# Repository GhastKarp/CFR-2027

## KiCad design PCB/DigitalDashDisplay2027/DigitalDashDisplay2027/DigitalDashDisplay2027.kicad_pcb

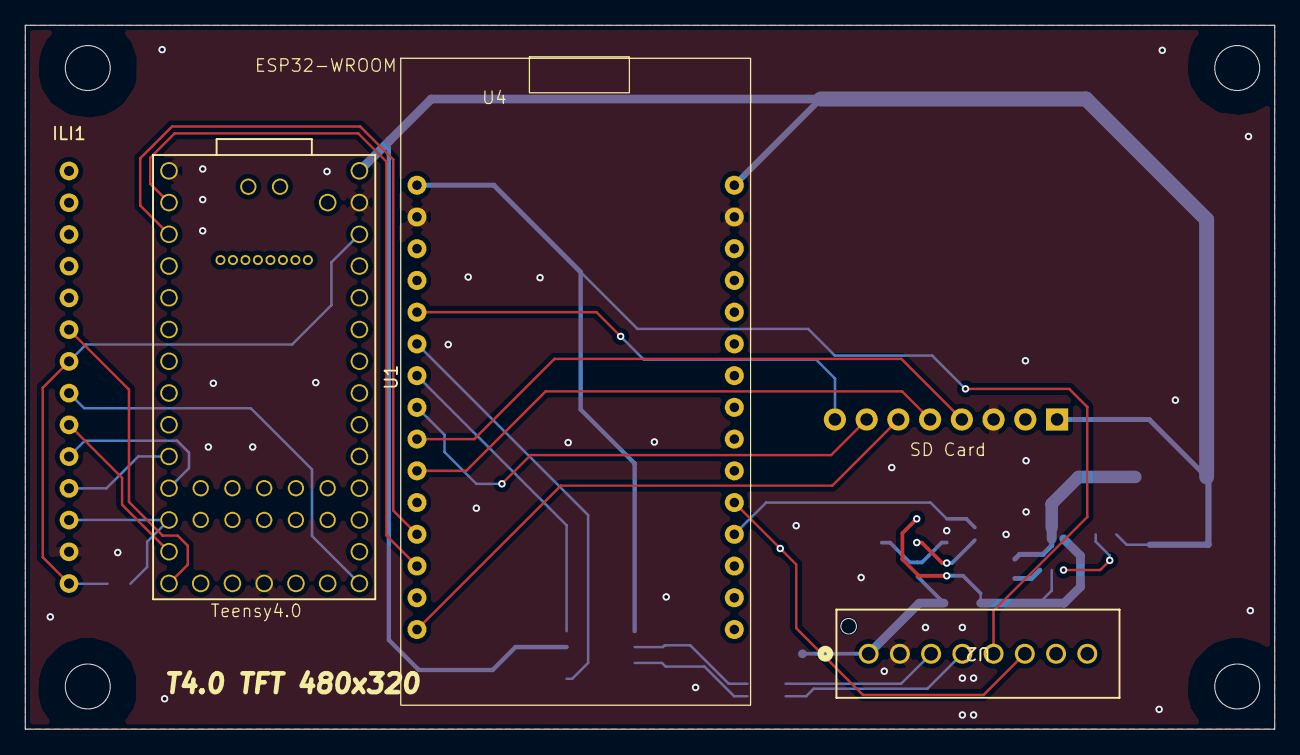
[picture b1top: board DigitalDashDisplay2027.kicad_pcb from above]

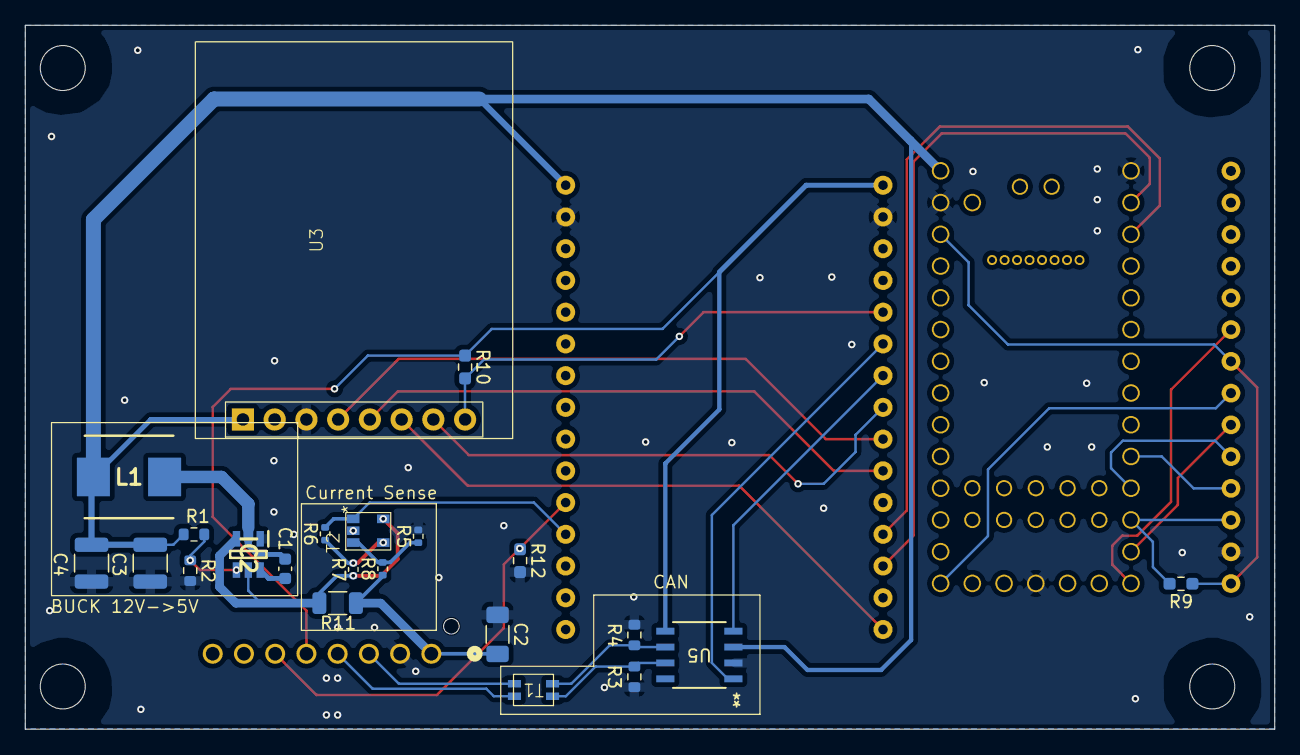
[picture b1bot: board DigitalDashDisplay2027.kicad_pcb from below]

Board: 2 copper layers, 100.0 x 56.3 mm, 26 parts (22 on the bottom side), 32 nets.

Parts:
C1: CC0603KRX7R7BB104; C_0603_1608Metric
C2: C3216X5R1E476MTJ00E; C_1206_3216Metric_Pad1.33x1.80mm_HandSolder
C3, C4: CL32A226KOJNNNE; C_1210_3225Metric
IC2: LMR51430YDDCR; SOT95P280X110-6N
ILI1: ILI9488
L1: PA4341.682ANLT; INDPM7166X300N
R1: ERA-3AED104V; R_0603_1608Metric
R2: ERJ-3EKF1372V; R_0603_1608Metric
R3, R4: 60; R_0603_1608Metric
R5, R6: 1.07M; R_0402_1005Metric
R7, R8: 2k; R_0402_1005Metric
R9, R10, R12: 10k; R_0603_1608Metric_Pad0.98x0.95mm_HandSolder
R11: CSR1206FT50L0; R_1206_3216Metric
T1: AC1210-110-C
T2: NCS2005SN1T1G
U1: Teensy4.0; Teensy40_SMT
U2: CONN08_533750810_MOL
U3: Adafruit 254
U4: ESP32
U5: TCAN1051VDRQ1; D8_TEX

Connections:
+5V: C3.1, C4.1, L1.2, R1.1, U1.33 (VIN), U3.1 (5V), U4.1 (VIN), U5.3 (VCC)
/3V3_ESP: R10.1, U2.5 (1), U4.30 (3V3), U5.5 (VIO)
/3V3_Teen: ILI1.7 (LED), ILI1.14 (VCC), R9.1, U1.31 (3V3)
/+12V: IC2.3 (VIN), IC2.5 (EN), R7.1, R11.1, T2.5 (V+)
/CAN Hi: T1.4 (AB), U2.4
/CAN Lo: T1.3 (SA), U2.3
/CANRx: U4.25 (RX2), U5.1 (TXD)
/CANTx: U4.24 (TX2), U5.4 (RXD)
/CurrentSense: C2.2, R8.1, R11.2, U2.1
/Current_0-3V3: R6.2, T2.1, U4.12 (D34)
/DAQ_Button: R12.1, U2.6 (2), U4.11 (D35)
/DC: ILI1.10 (DC/RS), U1.11 (9_OUT1C)
/GND: C2.1, C3.2, C4.2, IC2.1 (GND), ILI1.13 (Ground), R2.2, R3.2, R4.1, R5.2, R12.2, T2.2 (V-), U1.1 (GND), U1.17 (GND), U1.32 (GND), U2.2, U3.3 (GND), U4.2 (GND), U4.29 (GND), U5.2 (GND)
/Reset: ILI1.11 (Reset), U1.10 (8_TX2_IN1)
/SD_CD: R10.2, U3.8 (CD), U4.26 (D4)
/SD_CLK: U3.4 (CLK), U4.22 (D10)
/SD_CS: U3.7 (CS), U4.23 (D5)
/SD_MISO: U3.5 (D0), U4.21 (D19)
/SD_MOSI: U3.6 (DI), U4.16 (D23)
/TFT_CS: ILI1.12 (CS), R9.2, U1.12 (10_CS_MQSR)
/TFT_Clk: ILI1.8 (SCK), U1.20 (13_SCK_CRX1_LED)
/TFT_MISO: ILI1.6 (MISO), U1.14 (12_MISO_MQSL)
/TFT_MOSI: ILI1.9 (MOSI), U1.13 (11_MOSI_CTX1)
/TIn_EOut: U1.2 (0_RX1_CRX2_CS1), U4.18 (TX0)
/TOut_EIn: U1.3 (1_TX1_CTX2_MISO1), U4.19 (RX0)
unnamed: C1.1, IC2.6 (CB)
unnamed: IC2.4 (FB), R1.2, R2.1
unnamed: C1.2, IC2.2 (SW), L1.1
unnamed: R3.1, T1.1 (AA), U5.7 (CANH)
unnamed: R4.2, T1.2 (SB), U5.6 (CANL)
unnamed: R5.1, R8.2, T2.3 (+)
unnamed: R6.1, R7.2, T2.4 (-)

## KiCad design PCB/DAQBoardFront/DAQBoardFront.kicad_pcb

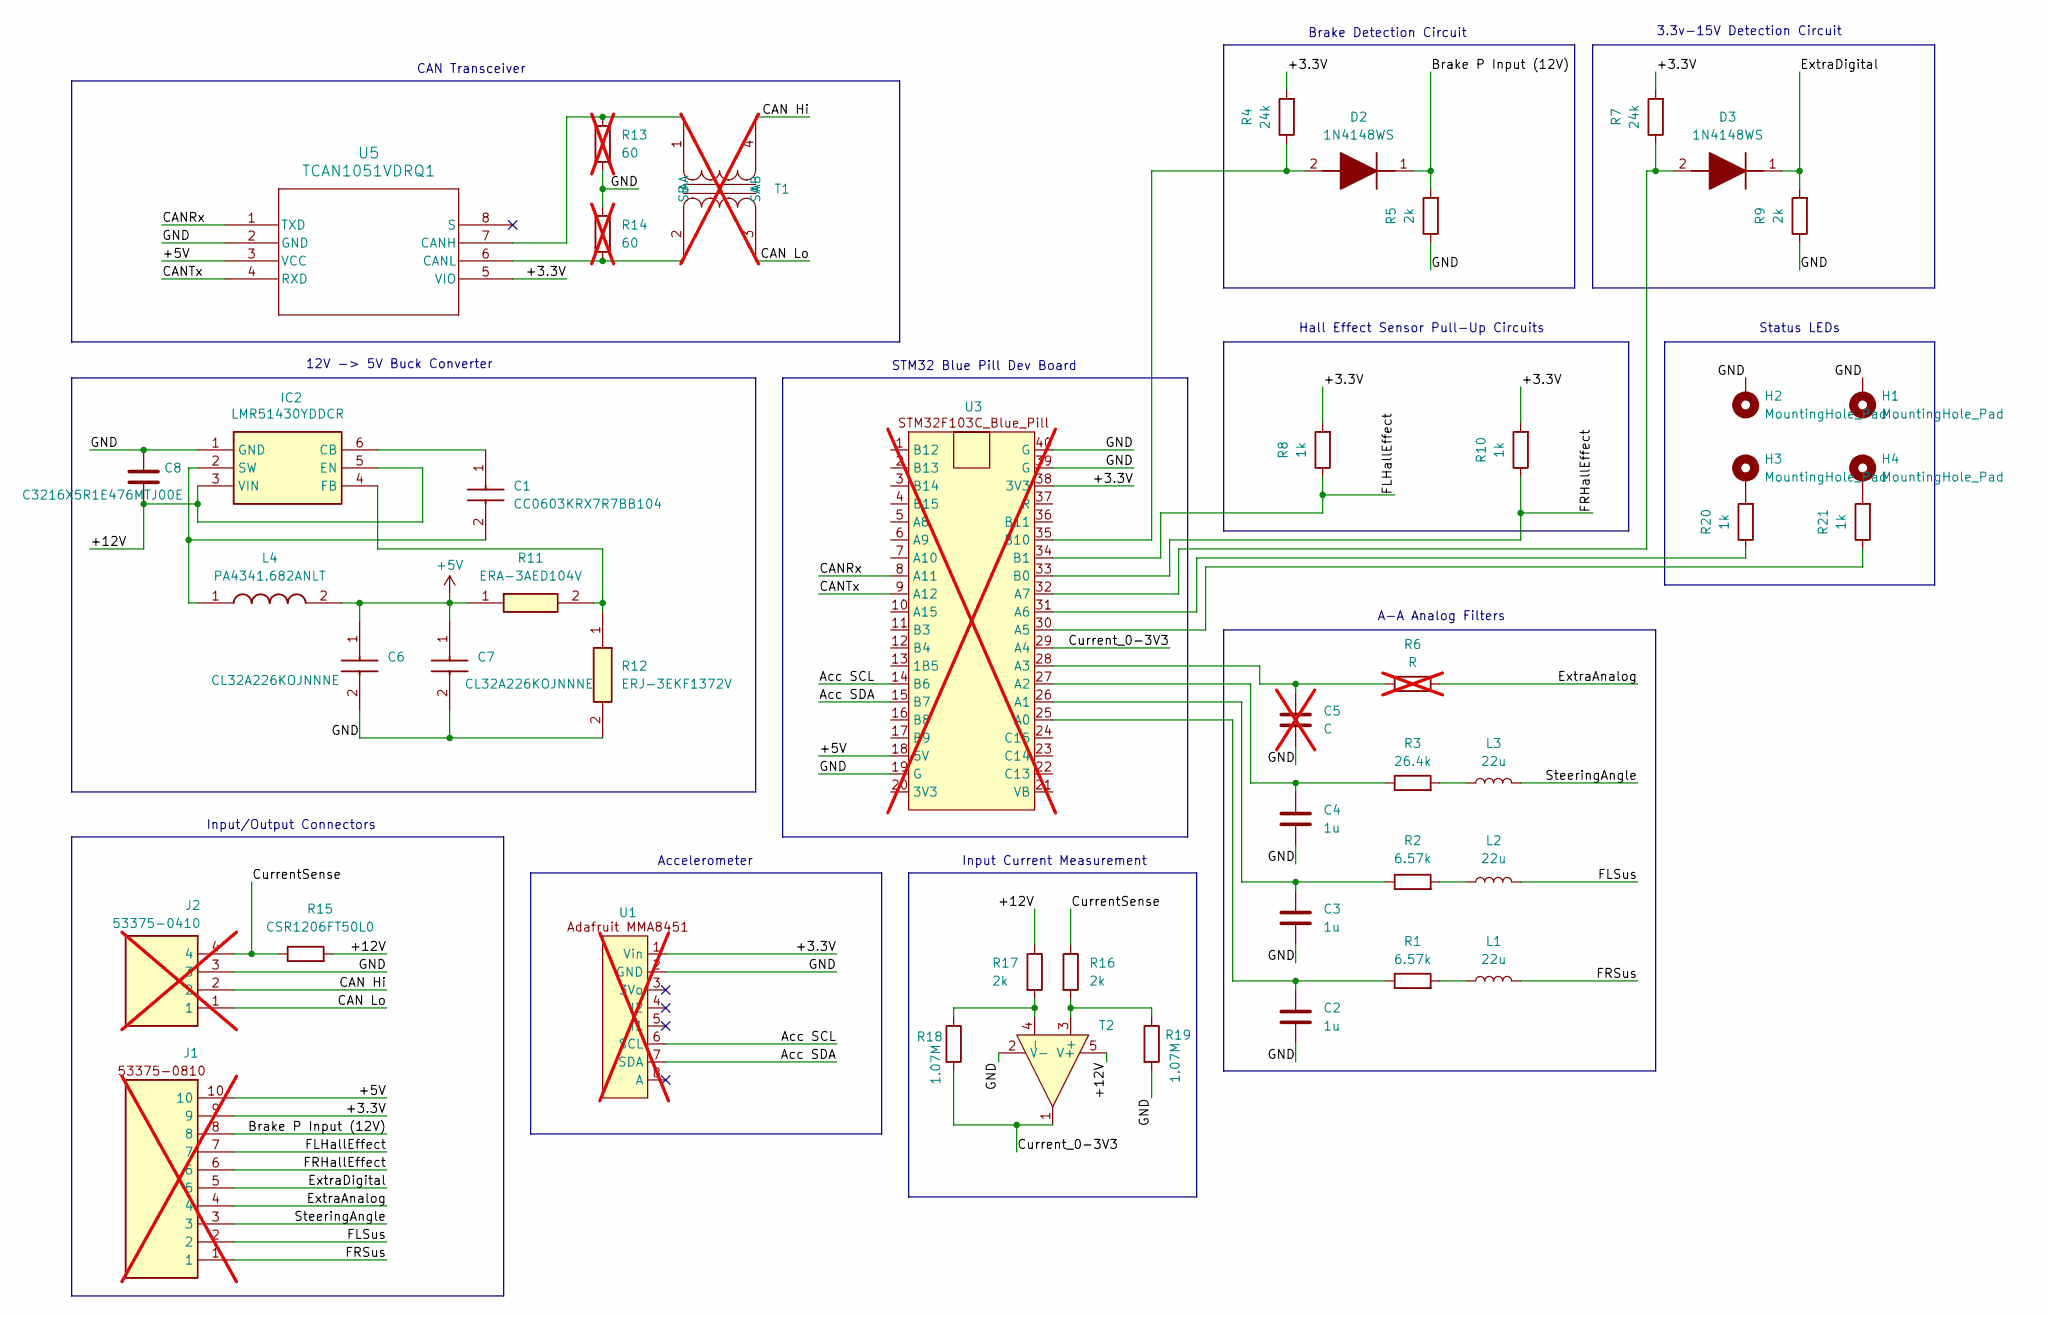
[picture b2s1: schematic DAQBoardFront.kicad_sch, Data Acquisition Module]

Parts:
C1: CC0603KRX7R7BB104; C_0603_1608Metric; Manufacturer_Part_Number CL05B104KO5NNNC; Mouser Part Number 187-CL05B104KO5NNNC
C2, C3, C4: 1u; C_0603_1608Metric_Pad1.08x0.95mm_HandSolder
C5: C; C_0603_1608Metric_Pad1.08x0.95mm_HandSolder; not fitted
C6, C7: CL32A226KOJNNNE; C_1210_3225Metric; Manufacturer_Part_Number CL32A226KOJNNNE
C8: C3216X5R1E476MTJ00E; C_1206_3216Metric_Pad1.33x1.80mm_HandSolder
D2, D3: 1N4148WS; SODFL2512X90N; Mouser Part Number 512-1N4148WS
H1, H2, H3, H4: MountingHole_Pad; PinHeader_1x01_P1.00mm_Vertical
IC2: LMR51430YDDCR; SOT95P280X110-6N; Manufacturer_Part_Number LMR51430YDDCR; Mouser Part Number 595-LMR51430YDDCR
J1: CONN10_533751010_MOL; not fitted
J2: 53375-0410; 0533750410; Mouser Part Number 538-53375-0410; not fitted
L1, L2, L3: 22u; L_0805_2012Metric_Pad1.05x1.20mm_HandSolder
L4: PA4341.682ANLT; INDPM7166X300N; Manufacturer_Part_Number PA4341.682ANLT; Mouser Part Number 673-PA4341.682ANLT
R1, R2: 6.57k; R_0603_1608Metric_Pad0.98x0.95mm_HandSolder
R3: 26.4k; R_0603_1608Metric_Pad0.98x0.95mm_HandSolder
R4, R7: 24k; LED_0603_1608Metric_Pad1.05x0.95mm_HandSolder; Rating 1/4W
R5, R9: 2k; R_0603_1608Metric_Pad0.98x0.95mm_HandSolder; Rating 1/4W
R6: R; R_0603_1608Metric_Pad0.98x0.95mm_HandSolder; not fitted
R8, R10, R20, R21: 1k; R_0603_1608Metric_Pad0.98x0.95mm_HandSolder; Rating 1/4W
R11: ERA-3AED104V; R_0603_1608Metric; Manufacturer_Part_Number ERA-3AED104V; Mouser Part Number 667-ERA-3AED104V
R12: ERJ-3EKF1372V; R_0603_1608Metric; Mouser Part Number 667-ERJ-3EKF1372V
R13, R14: 60; R_0603_1608Metric; not fitted
R15: CSR1206FT50L0; R_1206_3216Metric
R16, R17: 2k; R_0402_1005Metric
R18, R19: 1.07M; R_0402_1005Metric
T1: AC1210-110-C; not fitted
T2: NCS2005SN1T1G
U1: MODULE_2019; not fitted
U3: Blue-Pill; not fitted
U5: TCAN1051VDRQ1; D8_TEX

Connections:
+5V: C6.1, C7.1, J1.10, L4.2, R11.1, U3.18 (5V), U5.3 (VCC)
/+3.3V: J1.9, R4.2, R7.2, R8.2, R10.2, U1.1 (Vin), U3.38 (3V3), U5.5 (VIO)
/+12V: C8.2, IC2.3 (VIN), IC2.5 (EN), R15.2, R17.1, T2.5 (V+)
/Acc SCL: U1.6 (SCL), U3.14 (B6)
/Acc SDA: U1.7 (SDA), U3.15 (B7)
/Brake P Input (12V): D2.1 (K), J1.8, R5.2
/CAN Hi: J2.2, T1.4 (AB)
/CAN Lo: J2.1, T1.3 (SA)
/CANRx: U3.8 (A11), U5.1 (TXD)
/CANTx: U3.9 (A12), U5.4 (RXD)
/CurrentSense: J2.4, R15.1, R16.1
/Current_0-3V3: R18.2, T2.1, U3.29 (A4)
/ExtraAnalog: J1.4, R6.2
/ExtraDigital: D3.1 (K), J1.5, R9.2
/FLHallEffect: J1.7, R8.1, U3.34 (B1)
/FLSus: J1.2, L2.2
/FRHallEffect: J1.6, R10.1, U3.33 (B0)
/FRSus: J1.1, L1.2
/GND: C2.2, C3.2, C4.2, C5.2, C6.2, C7.2, C8.1, H1.1 (1_1), H2.1 (1_1), IC2.1 (GND), J2.3, R5.1, R9.1, R12.2, R13.2, R14.1, R19.2, T2.2 (V-), U1.2 (GND), U3.19 (G), U3.39 (G), U3.40 (G), U5.2 (GND)
/SteeringAngle: J1.3, L3.2
unnamed: D2.2 (A), R4.1, U3.35 (B10)
unnamed: D3.2 (A), R7.1, U3.32 (A7)
unnamed: H3.1 (1_1), R20.2
unnamed: H4.1 (1_1), R21.2
unnamed: C1.1, IC2.6 (CB)
unnamed: IC2.4 (FB), R11.2, R12.1
unnamed: C1.2, IC2.2 (SW), L4.1
unnamed: L1.1, R1.2
unnamed: L2.1, R2.2
unnamed: L3.1, R3.2
unnamed: R13.1, T1.1 (AA), U5.7 (CANH)
unnamed: R14.2, T1.2 (SB), U5.6 (CANL)
unnamed: R16.2, R19.1, T2.3 (+)
unnamed: R17.2, R18.1, T2.4 (-)
unnamed: C2.1, R1.1, U3.25 (A0)
unnamed: C3.1, R2.1, U3.26 (A1)
unnamed: C4.1, R3.1, U3.27 (A2)
unnamed: C5.1, R6.1, U3.28 (A3)
unnamed: R21.1, U3.30 (A5)
unnamed: R20.1, U3.31 (A6)

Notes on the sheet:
A-A Analog Filters
Hall Effect Sensor Pull-Up Circuits
Status LEDs
Brake Detection Circuit
Input/Output Connectors
12V -> 5V Buck Converter
Accelerometer
Input Current Measurement
3.3v-15V Detection Circuit
CAN Transceiver
STM32 Blue Pill Dev Board

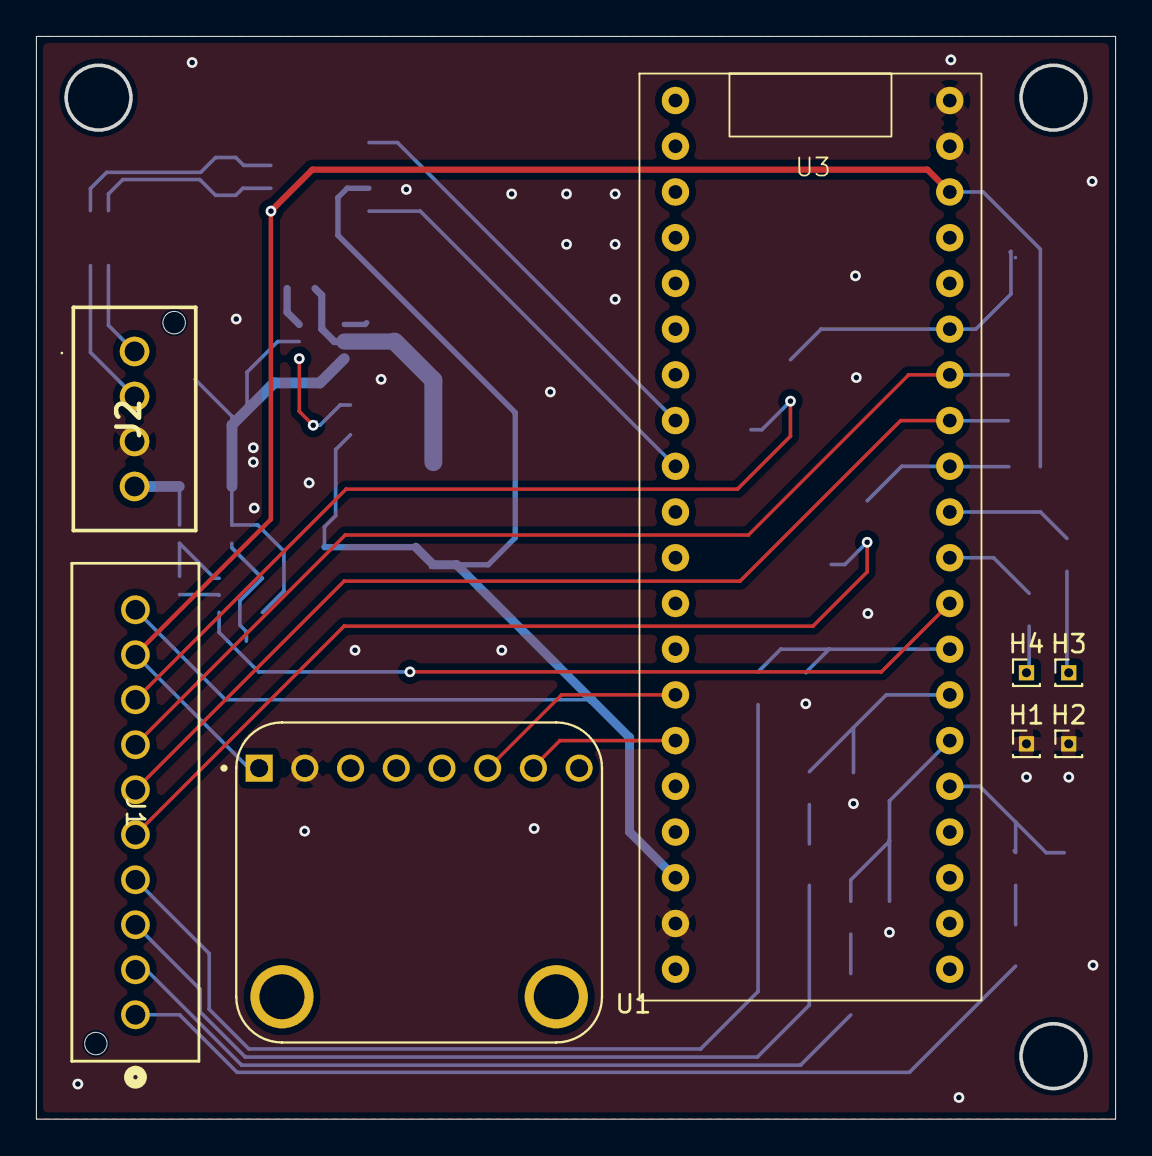
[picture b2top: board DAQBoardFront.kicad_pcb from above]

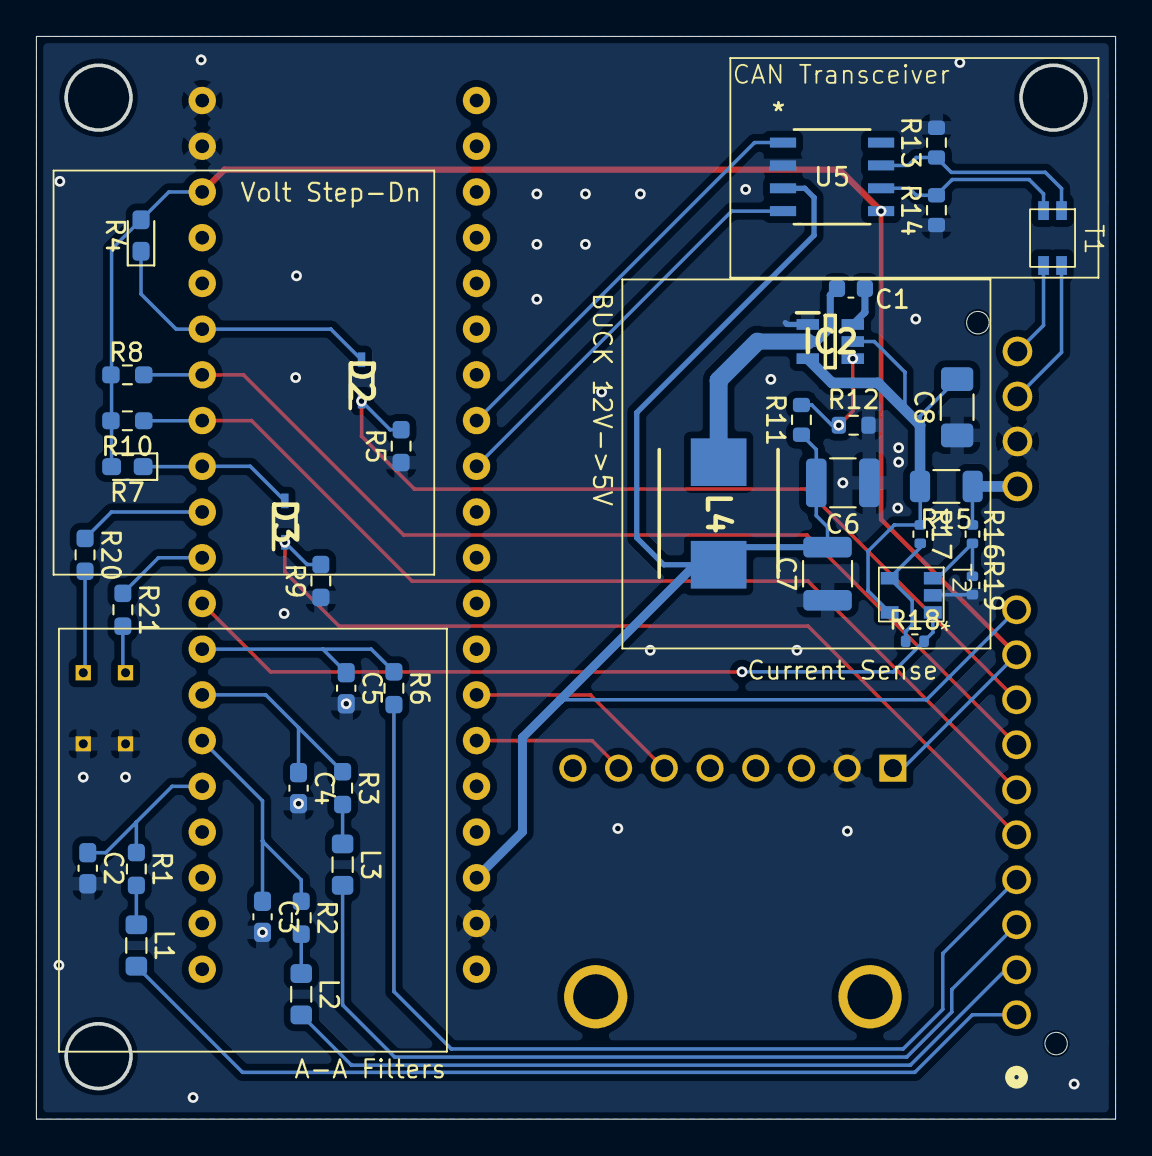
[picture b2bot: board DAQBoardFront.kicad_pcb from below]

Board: 2 copper layers, 59.8 x 60.0 mm, 47 parts (39 on the bottom side), 40 nets.

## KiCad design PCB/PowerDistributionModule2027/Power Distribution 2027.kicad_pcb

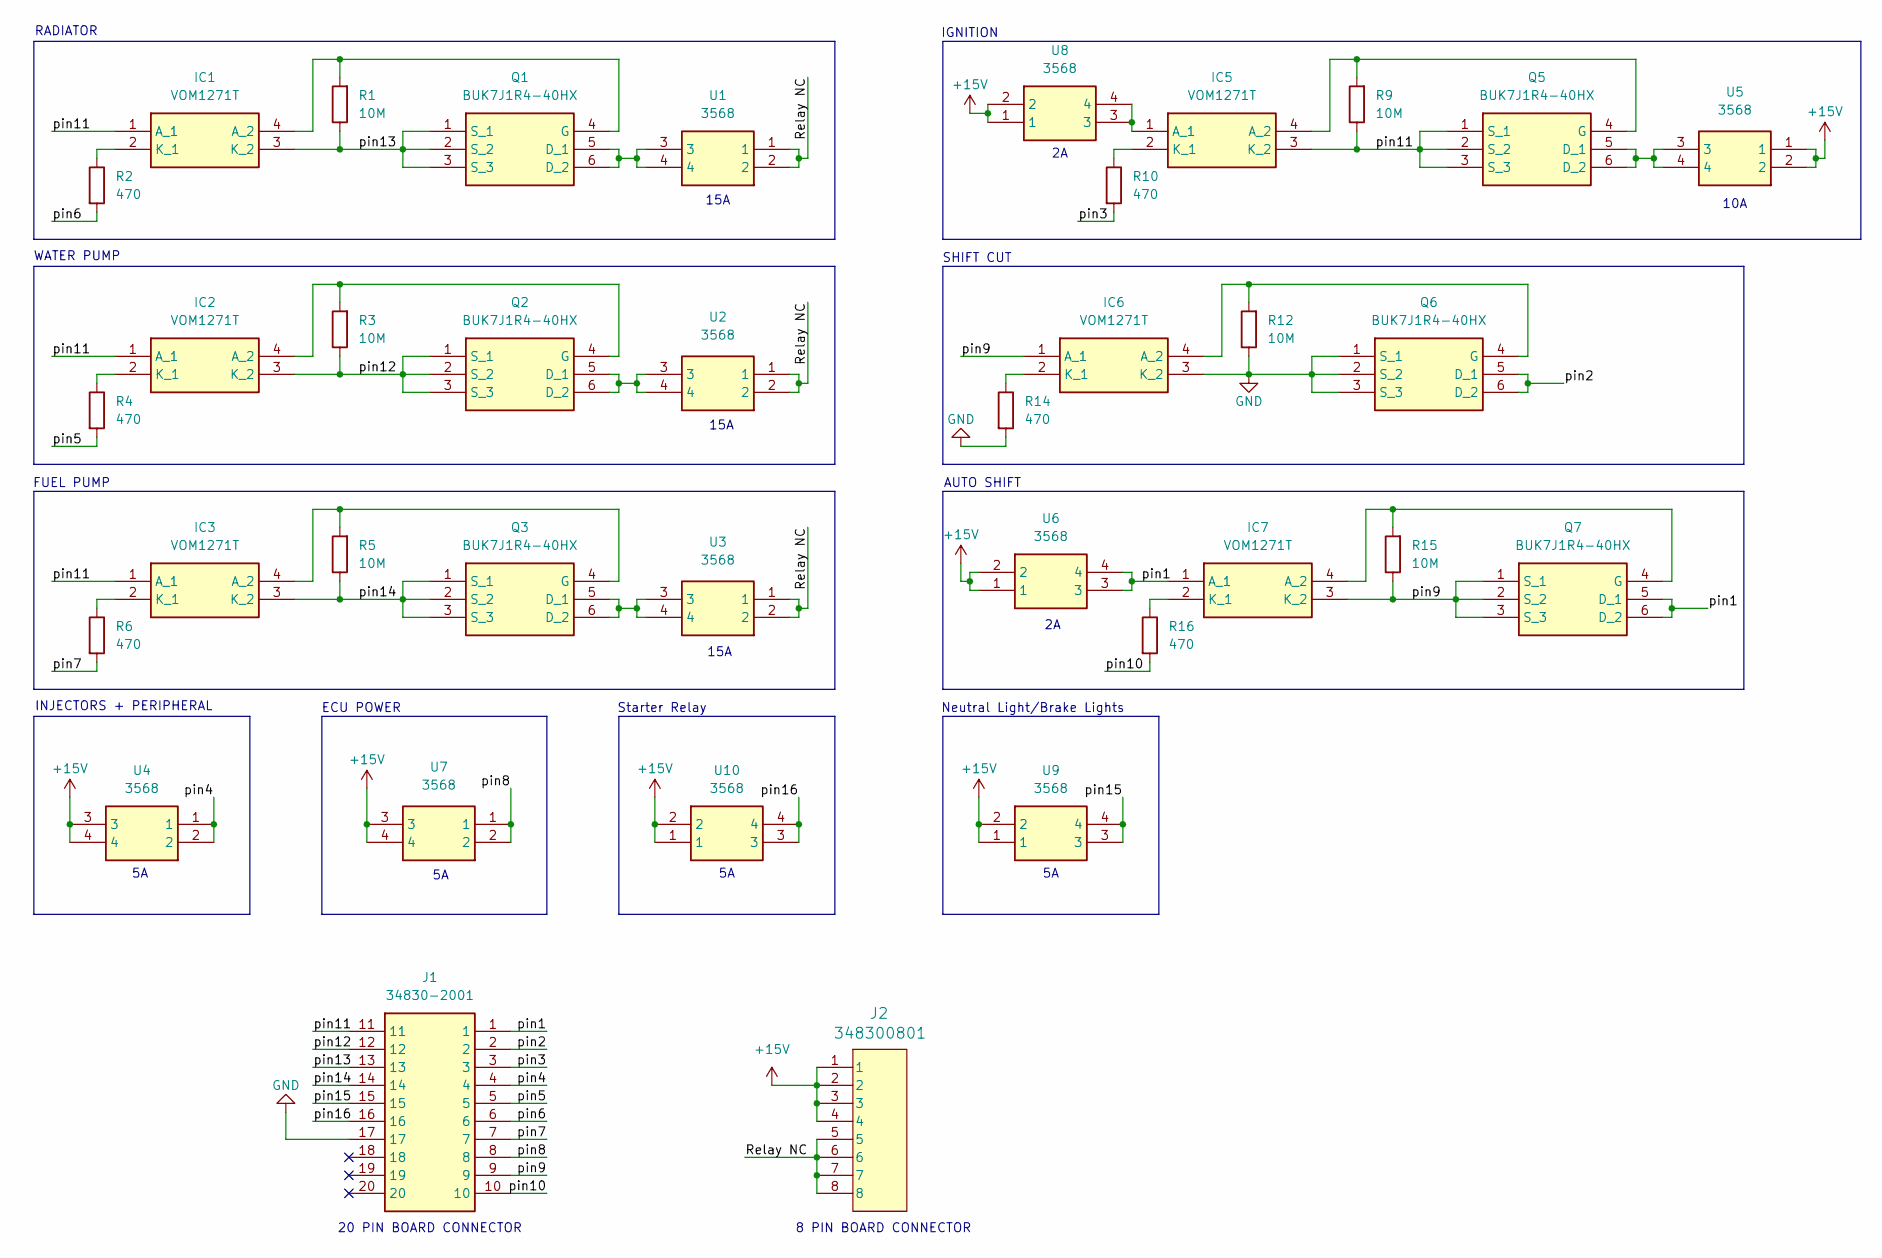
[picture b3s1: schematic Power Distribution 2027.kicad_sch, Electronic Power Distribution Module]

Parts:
IC1, IC2, IC3, IC5, IC6, IC7: VOM1271T; VOM1271T_FP; Mouser Part Number 78-VOM1271T
J1: 34830-2001; CONN_SD-34829-001_20_ST_MOL; Mouser Part Number 538-34830-2001
J2: 348300801; CONN_SD-34829-001_08_ST_MOL
Q1, Q2, Q3, Q5, Q6, Q7: BUK7J1R4-40HX; BUK7J1R440HX_FP; Mouser Part Number 771-BUK7J1R4-40HX
R1, R3, R5, R9, R12, R15: 10M; R_0603_1608Metric
R2, R4, R6, R10, R14, R16: 470; R_0603_1608Metric
U1, U2, U3, U4, U5, U6, U7, U8, U9, U10: 3568; 3568_FP; Mouser Part Number 534-3568

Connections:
+15V: J2.1, J2.2, J2.3, J2.4, U4.3, U4.4, U5.1, U5.2, U6.1, U6.2, U7.3, U7.4, U8.1, U8.2, U9.1, U9.2, U10.1, U10.2
/Relay NC: J2.5, J2.6, J2.7, J2.8, U1.1, U1.2, U2.1, U2.2, U3.1, U3.2
/pin1: IC7.1 (A_1), J1.1, Q7.5 (D_1), Q7.6 (D_2), U6.3, U6.4
/pin2: J1.2, Q6.5 (D_1), Q6.6 (D_2)
/pin3: J1.3, R10.2
/pin4: J1.4, U4.1, U4.2
/pin5: J1.5, R4.2
/pin6: J1.6, R2.2
/pin7: J1.7, R6.2
/pin8: J1.8, U7.1, U7.2
/pin9: IC6.1 (A_1), IC7.3 (K_2), J1.9, Q7.1 (S_1), Q7.2 (S_2), Q7.3 (S_3), R15.1
/pin10: J1.10, R16.2
/pin11: IC1.1 (A_1), IC2.1 (A_1), IC3.1 (A_1), IC5.3 (K_2), J1.11, Q5.1 (S_1), Q5.2 (S_2), Q5.3 (S_3), R9.1
/pin12: IC2.3 (K_2), J1.12, Q2.1 (S_1), Q2.2 (S_2), Q2.3 (S_3), R3.1
/pin13: IC1.3 (K_2), J1.13, Q1.1 (S_1), Q1.2 (S_2), Q1.3 (S_3), R1.1
/pin14: IC3.3 (K_2), J1.14, Q3.1 (S_1), Q3.2 (S_2), Q3.3 (S_3), R5.1
/pin15: J1.15, U9.3, U9.4
/pin16: J1.16, U10.3, U10.4
GND: IC6.3 (K_2), J1.17, Q6.1 (S_1), Q6.2 (S_2), Q6.3 (S_3), R12.1, R14.2
unnamed: IC1.4 (A_2), Q1.4 (G), R1.2
unnamed: IC1.2 (K_1), R2.1
unnamed: IC2.4 (A_2), Q2.4 (G), R3.2
unnamed: IC2.2 (K_1), R4.1
unnamed: IC3.4 (A_2), Q3.4 (G), R5.2
unnamed: IC3.2 (K_1), R6.1
unnamed: IC5.1 (A_1), U8.3, U8.4
unnamed: IC5.4 (A_2), Q5.4 (G), R9.2
unnamed: IC5.2 (K_1), R10.1
unnamed: IC6.4 (A_2), Q6.4 (G), R12.2
unnamed: IC6.2 (K_1), R14.1
unnamed: IC7.4 (A_2), Q7.4 (G), R15.2
unnamed: IC7.2 (K_1), R16.1
unnamed: Q1.5 (D_1), Q1.6 (D_2), U1.3, U1.4
unnamed: Q2.5 (D_1), Q2.6 (D_2), U2.3, U2.4
unnamed: Q3.5 (D_1), Q3.6 (D_2), U3.3, U3.4
unnamed: Q5.5 (D_1), Q5.6 (D_2), U5.3, U5.4

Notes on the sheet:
Starter Relay
20 PIN BOARD CONNECTOR
15A
Neutral Light/Brake Lights
ECU POWER
8 PIN BOARD CONNECTOR
INJECTORS + PERIPHERAL
IGNITION
RADIATOR
10A
FUEL PUMP
AUTO SHIFT
SHIFT CUT
WATER PUMP

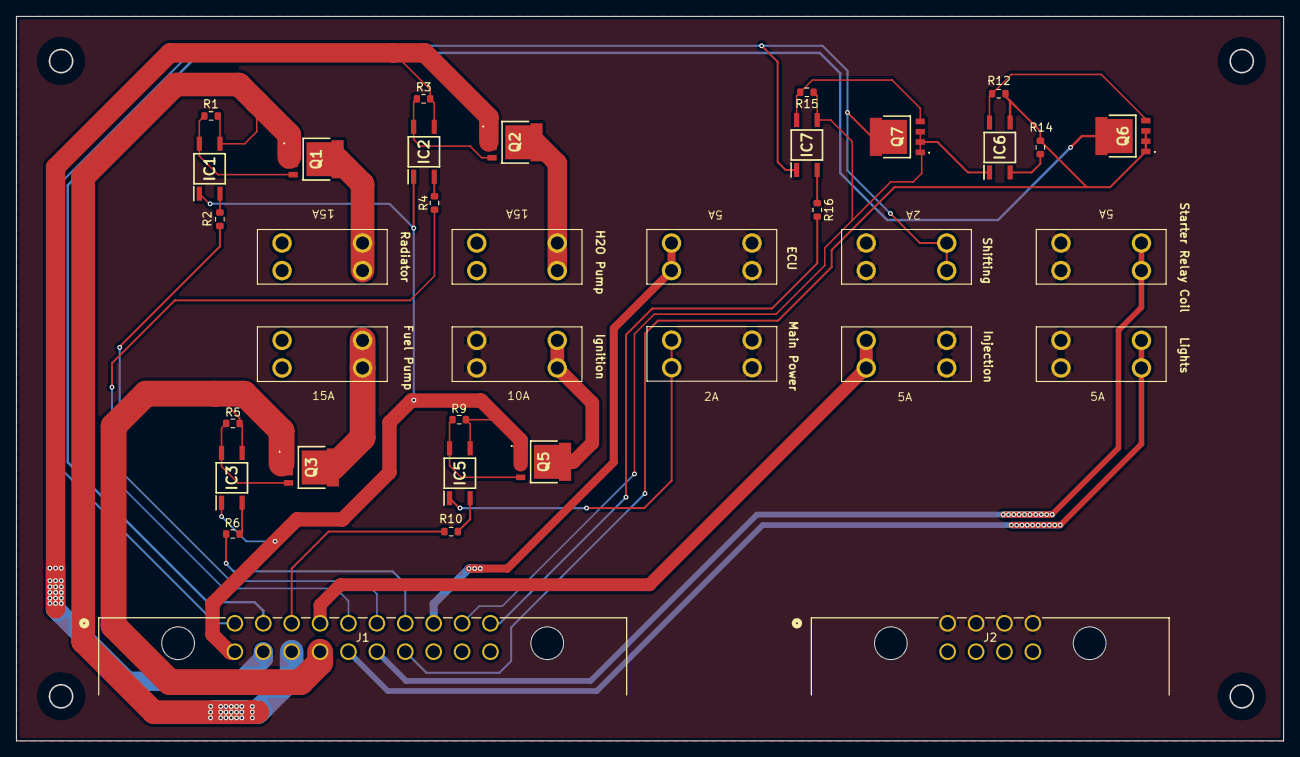
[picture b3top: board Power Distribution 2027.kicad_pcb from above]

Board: 2 copper layers, 156.0 x 89.1 mm, 36 parts (0 on the bottom side), 36 nets.

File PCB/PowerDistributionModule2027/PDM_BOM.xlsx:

Comment | Designator | Footprint | JLCPCB Part #
VOM1271T | IC1, IC2, IC3, IC5, IC6, IC7 | VOM1271T_FP | C146286
BUK7J1R4-40HX | Q1, Q2, Q3, Q5, Q6, Q7 | BUK7J1R440HX_FP | C458262
10M | R1, R3, R5, R9, R12, R15 | R_0603_1608Metric | C177278
470 | R2, R4, R6, R10, R14, R16 | R_0603_1608Metric | C177340
 | `

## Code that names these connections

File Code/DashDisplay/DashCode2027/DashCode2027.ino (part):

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// TFT Pin Definitions
#define TFT_RST   8
#define TFT_DC    9
#define TFT_CS    10
#define TFT_MOSI  11
#define TFT_MISO  12
#define TFT_CLK   13
// -------------------

// Define TFT display
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void setup(){

  // Initialize 
  pinMode(TFT_CS, INPUT_PULLUP);
  pinMode(TFT_CLK, INPUT_PULLUP);
  pinMode(TFT_MISO, INPUT_PULLUP);
  pinMode(TFT_MOSI, INPUT_PULLUP);

  // Serial settings
  Serial.begin(9600); // USB Debug Serial
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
